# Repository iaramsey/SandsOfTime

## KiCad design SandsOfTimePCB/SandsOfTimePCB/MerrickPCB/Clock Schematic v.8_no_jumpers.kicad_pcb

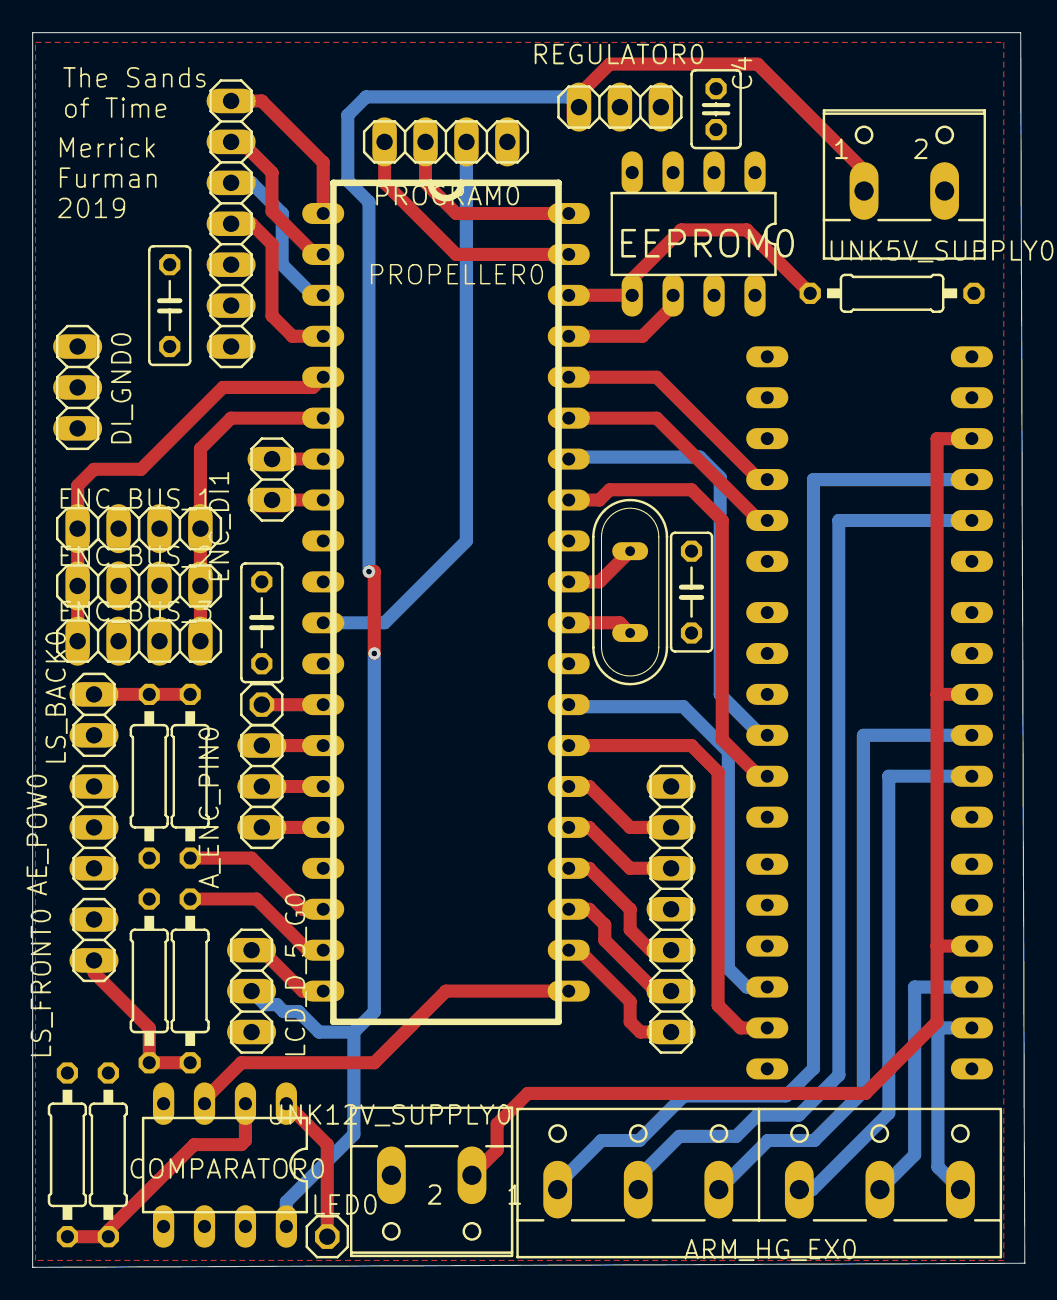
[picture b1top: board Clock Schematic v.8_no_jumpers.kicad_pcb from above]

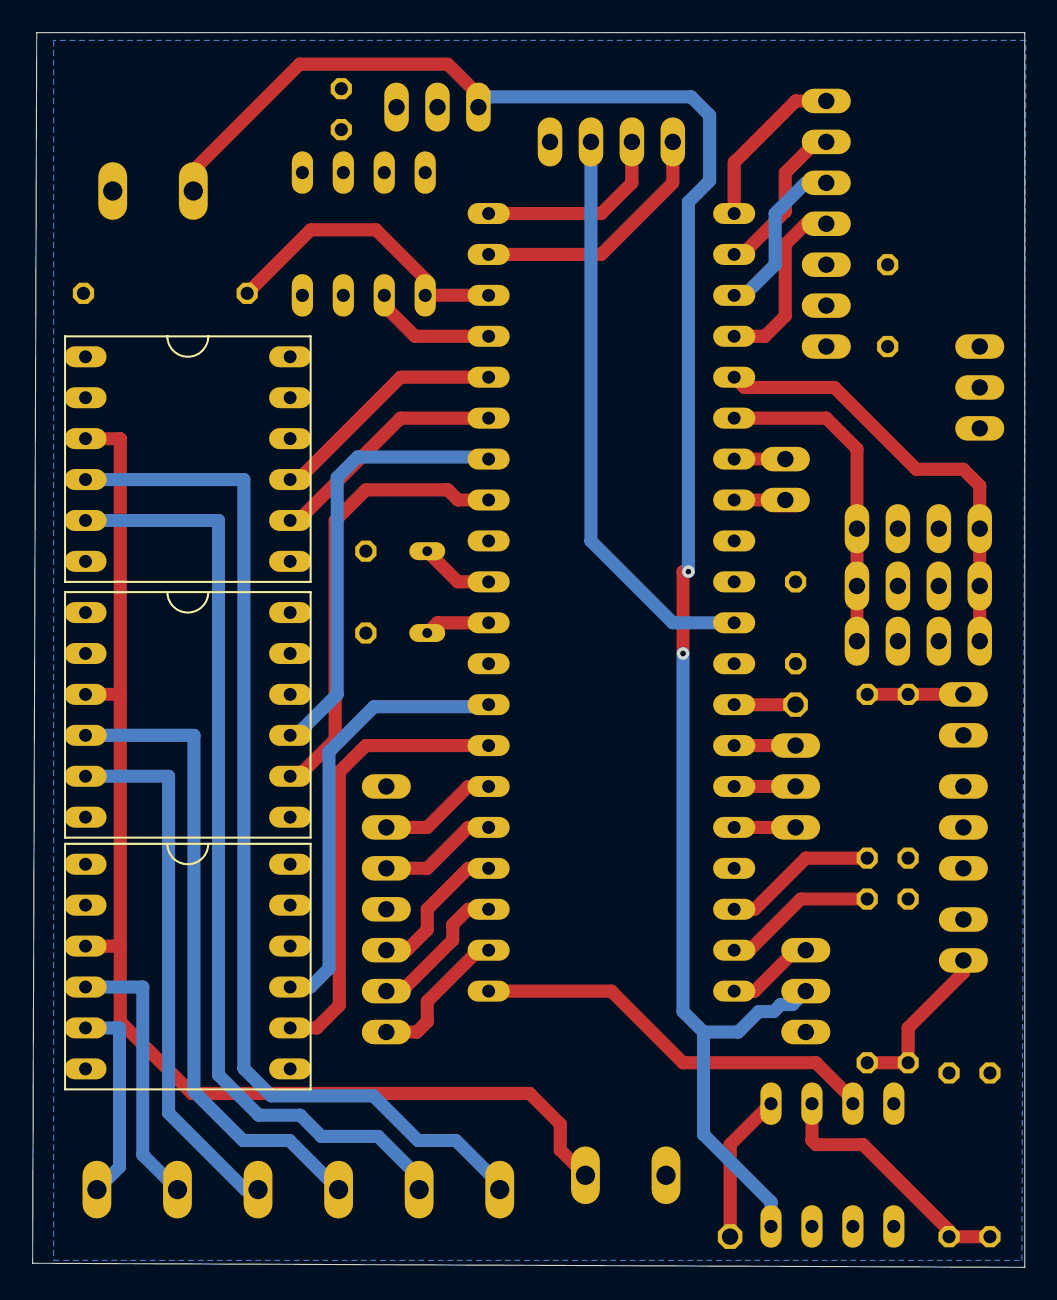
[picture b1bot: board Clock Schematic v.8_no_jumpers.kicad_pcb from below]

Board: 2 copper layers, 61.6 x 76.6 mm, 37 parts (3 on the bottom side), 48 nets.

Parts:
AE_POW0: 1X03
ARM0: DRV
ARM_HG_EX0: W237-6
A_ENC_PIN0: 1X03
C1: 0.1uF; C050-025X075
C2, C3: C050-025X075
C4: 0.1uF; C025-030X050
COMPARATOR0: MAX907CPA; DIL08
DI_GND0: 1X03
EEPROM0: 24LC256P; DIL8
ENC_BUS_1, ENC_BUS_2, ENC_BUS_3: 1X04
ENC_DI1: 1X02
EXTEND0: DRV
HG0: DRV
JP1: 1X07
JP3: 1X01
JS0: 1X07
LCD_D_5_G0: 1X03
LED0: 1X01
LS_BACK0: 1X02
LS_FRONT0: 1X02
PROGRAM0: 1X04
PROPELLER0: P8X32A-D40
Q1: QS
R1, R2: 300; 0207_10
R3, R5, R7: 10k; 0207_10
R4, R6: 470; 0207_10
REGULATOR0: 1X03
UNK5V_SUPPLY0, UNK12V_SUPPLY0: W237-102

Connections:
+3V3: AE_POW0.1, ARM0.P$7, C1.1, C2.1, C3.1, C4.1, EEPROM0.8, ENC_BUS_1.2, ENC_BUS_2.2, ENC_BUS_3.2, EXTEND0.P$7, HG0.P$7, JP1.6, JS0.1, LS_BACK0.1, LS_FRONT0.1, PROPELLER0.12, PROPELLER0.32, R1.2, R7.2, REGULATOR0.1
+5V: COMPARATOR0.8, LCD_D_5_G0.2, REGULATOR0.3, UNK5V_SUPPLY0.1
+12V: ARM0.P$4, EXTEND0.P$4, HG0.P$4, UNK12V_SUPPLY0.1
ENC_CLK: ENC_BUS_1.4, ENC_BUS_2.4, ENC_BUS_3.4, PROPELLER0.6
ENC_CS: ENC_BUS_1.1, ENC_BUS_2.1, ENC_BUS_3.1, PROPELLER0.5
GND: AE_POW0.2, AE_POW0.3, ARM0.P$1, ARM0.P$5, ARM0.P$6, ARM0.P$8, ARM0.P$9, ARM0.P$12, C1.2, C2.2, C3.2, C4.2, COMPARATOR0.4, COMPARATOR0.5, COMPARATOR0.6, COMPARATOR0.7, DI_GND0.1, DI_GND0.2, DI_GND0.3, EEPROM0.1, EEPROM0.2, EEPROM0.3, EEPROM0.4, EEPROM0.7, ENC_BUS_1.3, ENC_BUS_2.3, ENC_BUS_3.3, EXTEND0.P$1, EXTEND0.P$5, EXTEND0.P$6, EXTEND0.P$8, EXTEND0.P$9, EXTEND0.P$12, HG0.P$1, HG0.P$5, HG0.P$6, HG0.P$8, HG0.P$9, HG0.P$12, JP1.7, JS0.4, LCD_D_5_G0.1, PROGRAM0.1, PROPELLER0.9, PROPELLER0.10, PROPELLER0.29, R2.1, R3.1, R5.1, REGULATOR0.2, UNK5V_SUPPLY0.2, UNK12V_SUPPLY0.2
unnamed: ENC_DI1.1, PROPELLER0.7
unnamed: JS0.5, PROPELLER0.24
unnamed: JS0.6, PROPELLER0.23
unnamed: JS0.7, PROPELLER0.22
unnamed: JS0.3, PROPELLER0.25
unnamed: JS0.2, PROPELLER0.26
unnamed: LCD_D_5_G0.3, PROPELLER0.20
unnamed: ENC_DI1.2, PROPELLER0.8
unnamed: COMPARATOR0.1, LED0.1
unnamed: PROPELLER0.31, Q1.2
unnamed: COMPARATOR0.2, R1.1, R2.2
unnamed: PROPELLER0.30, Q1.1
unnamed: PROPELLER0.19, R4.1
unnamed: LS_BACK0.2, R5.2, R6.2
unnamed: PROPELLER0.18, R6.1
unnamed: EEPROM0.6, PROPELLER0.37
unnamed: ARM0.P$11, PROPELLER0.27
unnamed: PROGRAM0.4, PROPELLER0.39
unnamed: PROGRAM0.3, PROPELLER0.40
unnamed: EEPROM0.5, PROPELLER0.38, R7.1
unnamed: COMPARATOR0.3, PROPELLER0.21
unnamed: ARM0.P$10, PROPELLER0.28
unnamed: HG0.P$11, PROPELLER0.33
unnamed: HG0.P$10, PROPELLER0.34
unnamed: EXTEND0.P$11, PROPELLER0.35
unnamed: PROGRAM0.2, PROPELLER0.11
unnamed: LS_FRONT0.2, R3.2, R4.2
unnamed: EXTEND0.P$10, PROPELLER0.36
unnamed: ARM_HG_EX0.1, EXTEND0.P$3
unnamed: ARM_HG_EX0.2, EXTEND0.P$2
unnamed: ARM_HG_EX0.3, HG0.P$3
unnamed: ARM_HG_EX0.4, HG0.P$2
unnamed: ARM0.P$3, ARM_HG_EX0.5
unnamed: ARM0.P$2, ARM_HG_EX0.6
unnamed: JP3.1, PROPELLER0.13
unnamed: A_ENC_PIN0.1, PROPELLER0.14
unnamed: A_ENC_PIN0.2, PROPELLER0.15
unnamed: A_ENC_PIN0.3, PROPELLER0.16
RTC_CLK: JP1.4, PROPELLER0.4
RTC_CS: JP1.1, PROPELLER0.1
RTC_SI: JP1.2, PROPELLER0.2
RTC_SO: JP1.3, PROPELLER0.3

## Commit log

2023-02-20 added kicad files
2023-03-15 added files from old project
2023-03-15 Hudson stuff
2023-03-20 Structure and Garner code
2023-03-22 finished DS3234 and motor drivers code
2023-03-29 So much things
2023-04-12 A whole lotta stuff
2023-05-01 worked on testing LCD
2023-05-02 added LED code to turn white for the hourglass being rotated
2023-05-03 Temporary
2023-05-03 removal of outa. ina. and dira.
2023-05-03 comments?
2023-05-06 cleanup
2023-05-11 Working demos
